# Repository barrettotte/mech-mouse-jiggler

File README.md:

# mech-mouse-jiggler

A very impractical and stupid mouse jiggler using a crank mechanism, 12V DC motor, and a PWM circuit.

## Purpose

I wanted a basic project with some gears, a mechanical movement, and a DC motor. 
So this was the simplest thing I could think of; Move a mouse back and forth.

The mechanical movement and gears gave me more experience with components/joints in Fusion 360.
I also took the opportunity to learn KiCad and design a PCB for my basic PWM circuit.

## Finished Project

Definitely not perfect and I kept finding flaws. But, it was good enough for the project scope I made.

https://user-images.githubusercontent.com/15623775/172682833-343187b7-290f-4d06-a3b5-5a9f5e372b6b.mp4

https://user-images.githubusercontent.com/15623775/172682868-b304a3e7-49c9-4841-98fb-ab1815b85bfa.mp4

## PWM Circuit

## References

- [507 Movements #92](http://507movements.com/mm_092.html)
- [507 Movements #114](http://507movements.com/mm_114.html)
- [KHK Gear Reference](https://khkgears.net/new/gear_knowledge/gear_technical_reference/involute_gear_profile.html)
- [555 Timer PWM circuit](http://www.555-timer-circuits.com/motor-pwm.html)

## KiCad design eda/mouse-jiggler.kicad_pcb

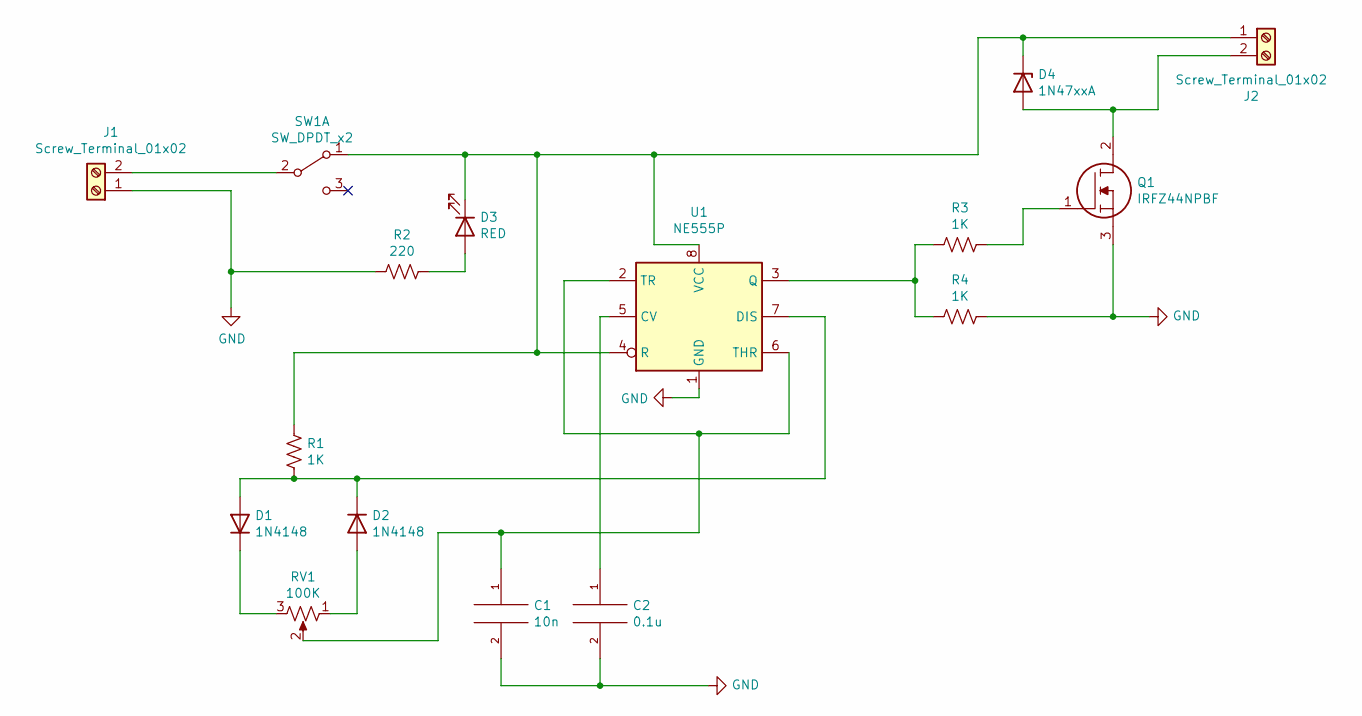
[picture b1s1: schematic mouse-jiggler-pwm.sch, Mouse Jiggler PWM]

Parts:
C1: 10n; C_Disc_D3.8mm_W2.6mm_P2.50mm
C2: 0.1u; C_Disc_D3.8mm_W2.6mm_P2.50mm
D1, D2: 1N4148; D_DO-35_SOD27_P7.62mm_Horizontal
D3: RED; LED_D5.0mm
D4: 1N47xxA; D_DO-41_SOD81_P10.16mm_Horizontal
J1, J2: Screw_Terminal_01x02; TerminalBlock_bornier-2_P5.08mm
Q1: IRFZ44NPBF; TO254P483X1016X1994-3P; Mouser Part Number 942-IRFZ44NPBF
R1, R3, R4: 1K; R_Axial_DIN0207_L6.3mm_D2.5mm_P10.16mm_Horizontal
R2: 220; R_Axial_DIN0207_L6.3mm_D2.5mm_P10.16mm_Horizontal
RV1: 100K; Potentiometer_Alps_RK163_Single_Horizontal
SW1: SW_DPDT_x2; 100SP1T1B4M2QE
U1: NE555P; DIP-8_W7.62mm_Socket

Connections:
GND: C1.2, C2.2, J1.1, Q1.3, R2.2, R4.1, U1.1 (GND)
unnamed: C1.1, RV1.2, U1.2 (TR), U1.6 (THR)
unnamed: C2.1, U1.5 (CV)
unnamed: D1.1 (K), RV1.3
unnamed: D1.2 (A), D2.1 (K), R1.2, U1.7 (DIS)
unnamed: D2.2 (A), RV1.1
unnamed: D3.1 (K), D4.1 (K), J2.1, R1.1, SW1.1 (A), U1.4 (R), U1.8 (VCC)
unnamed: D3.2 (A), R2.1
unnamed: D4.2 (A), J2.2, Q1.2
unnamed: J1.2, SW1.2 (B)
unnamed: Q1.1, R3.1
unnamed: R3.2, R4.2, U1.3 (Q)

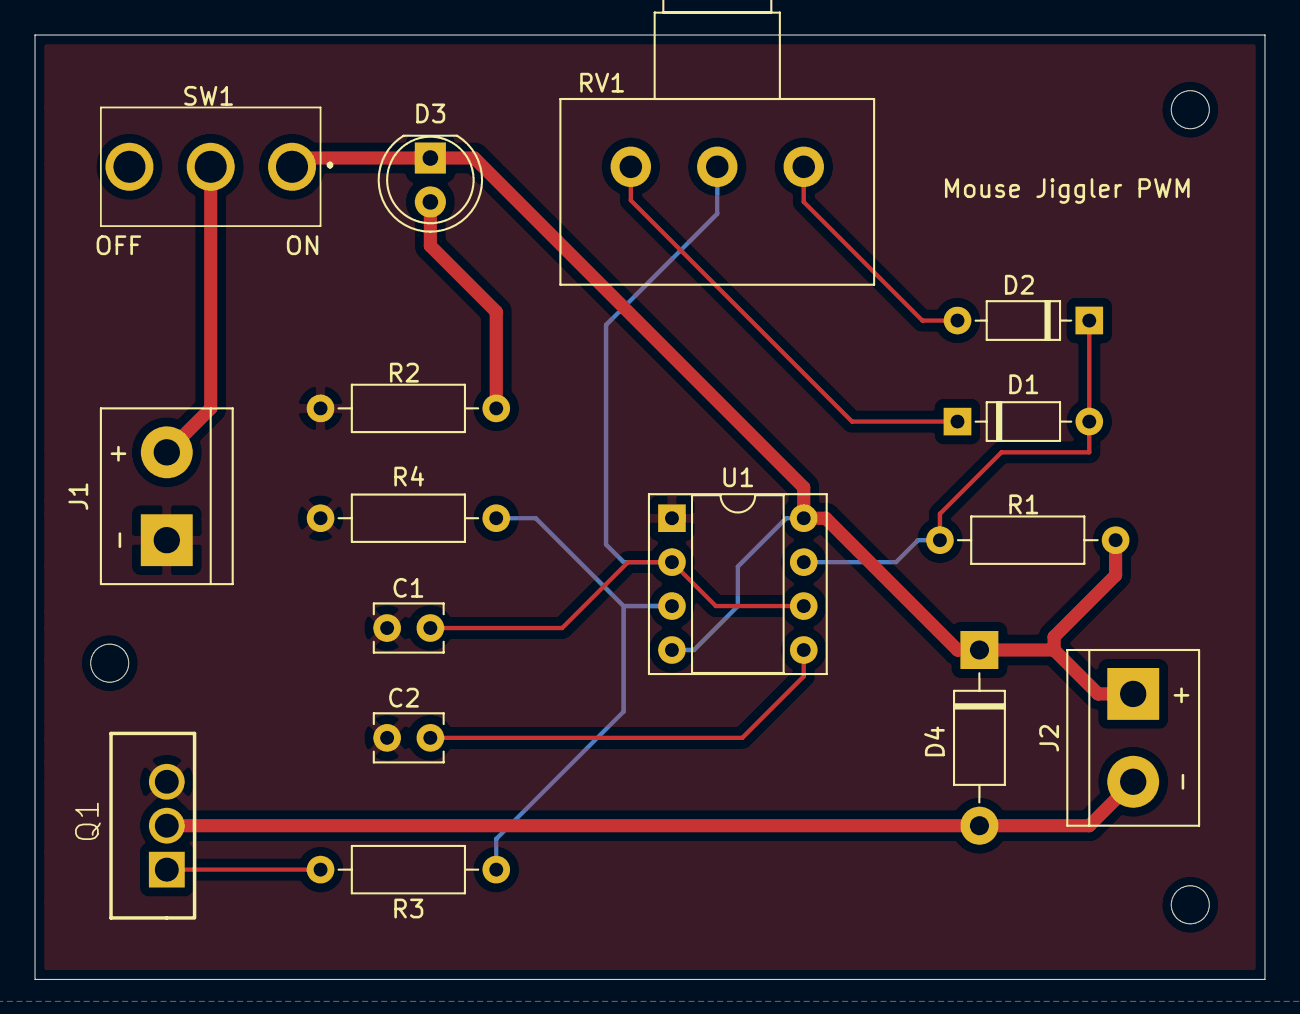
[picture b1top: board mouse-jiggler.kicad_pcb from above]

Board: 2 copper layers, 71.1 x 54.6 mm, 16 parts (0 on the bottom side), 12 nets.

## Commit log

2022-03-17 test 114 movement
2022-03-18 movement 114 test
2022-03-21 114 test
2022-05-20 movement 92 test
2022-05-25 base design
2022-05-27 basic components cad
2022-05-27 basic kicad schematic
2022-05-29 fix mouse clamp
2022-05-29 pcb footprint layout
2022-05-29 fix toggle switch footprint and generate gerber
2022-05-29 add PWM circuit CAD to fusion 360 project
2022-05-30 fix Gerber zip
2022-05-30 tweak gear bevel gear, add wheel spacer, add motor mount
2022-05-30 double thickness of motor mount
2022-06-02 tweak wheel and coupler dimensions
2022-06-02 added electronics base cover
2022-06-02 tweak and add pry hole to electronics cover
2022-06-07 add mechanical bom
2022-06-08 add images
2022-06-08 add motion study gif
2022-06-08 add finished pictures and test videos
2022-06-08 fix video links

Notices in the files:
eda/mouse-jiggler-pwm.sch:
License: MIT
